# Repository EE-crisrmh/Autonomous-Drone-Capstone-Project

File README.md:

# LumaWay 🌄

> **A GPS-guided autonomous drone system that guides lost hikers back to safety.**

---

## The Problem

Every year, thousands of hikers get lost on trails across the United States. Terrain looks the same in every direction. Cell service is gone. Panic sets in. Search and rescue teams can take hours to respond — and in the mountains, hours matter.

Current solutions require hikers to stay still and wait. LumaWay flips that. Instead of waiting to be found, the hiker gets found — and then guided home.

---

## What LumaWay Does

LumaWay is an autonomous drone system built for one purpose: get a lost hiker back on the trail.

Here's how it works:

1. **Before the hike**, the hiker opens the LumaWay app and starts a session. The app passively records their GPS trail as they walk in — no interaction needed, just like a fitness tracker running in the background.

2. **If they get lost**, they hit the SOS button. The app sends their current GPS location and their recorded trail path to the LumaWay ground station.

3. **The drone launches autonomously**, navigates to the hiker's GPS coordinates, and locates them.

4. **LumaWay leads them out.** The drone flies the recorded trail path in reverse — slowly, at walking pace — using a bright LED and audio signal to guide the hiker back to the trailhead. Follow the light. That's it.

No payload to drop. No complex robotics. Just a reliable, visible guide in the sky when you need it most.

---

## Why a Drone

A drone can cover terrain a person can't. It flies over downed trees, river crossings, and steep ridgelines. It doesn't get lost. It doesn't get tired. And it can reach a hiker in minutes rather than hours.

LumaWay isn't trying to replace search and rescue — it's a first response that buys time, reduces panic, and gets people moving in the right direction before conditions get worse.

---

## The System

LumaWay is built across three integrated components:

**Custom Flight Controller (Hardware)**
A 4-layer custom PCB built around dual STM32 microcontrollers — one for navigation, one for I/O. Onboard sensors include dual IMUs (ICM-20689, ICM-20602), a barometer (MS5611), and a magnetometer (IST8310) for full attitude and altitude awareness. Designed and manufactured in-house.

**Onboard Computing (Autonomy)**
An NVIDIA Jetson Nano handles high-level autonomy — GPS waypoint navigation, computer vision for hiker confirmation, and communication with the ground station over a wireless link.

**LumaWay App (Interface)**
A mobile app for hikers. Records the trail on the way in. Sends SOS with one tap. Shows the drone's live position on a map so rescue coordinators can monitor the situation in real time.

---

## Project Goals

- Demonstrate fully autonomous GPS-guided navigation to a target location
- Achieve stable hover and guided return-path flight in outdoor conditions
- Build a functional mobile app with trail recording and SOS capability
- Integrate onboard vision for hiker detection and confirmation
- Complete a full end-to-end demo: SOS sent → drone launches → hiker guided back

---

## Status

🔧 **In development** — UW Bothell Capstone Project, 2026–2027

---

## Team

Built by a four-person Electrical Engineering capstone team at the University of Washington Bothell, supervised by Dr. Hannachi.

- Cris R. Martinez Hernandez
- Abraham Chen
- Frank Ma
- Howard Sin

---

## Built With

- STM32F405 / STM32F103 (flight controller MCUs)
- NVIDIA Jetson Nano (onboard compute)
- T-Motor MN2806 Antigravity motors
- KiCad (PCB design)
- PlatformIO (firmware)
- Python / OpenCV (computer vision)
- React Native (mobile app)

---

*LumaWay — your way home made easy*

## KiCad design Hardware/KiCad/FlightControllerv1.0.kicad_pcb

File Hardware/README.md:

Hardware files for PORT Flight Controller v1.0 + ESCs v1.0

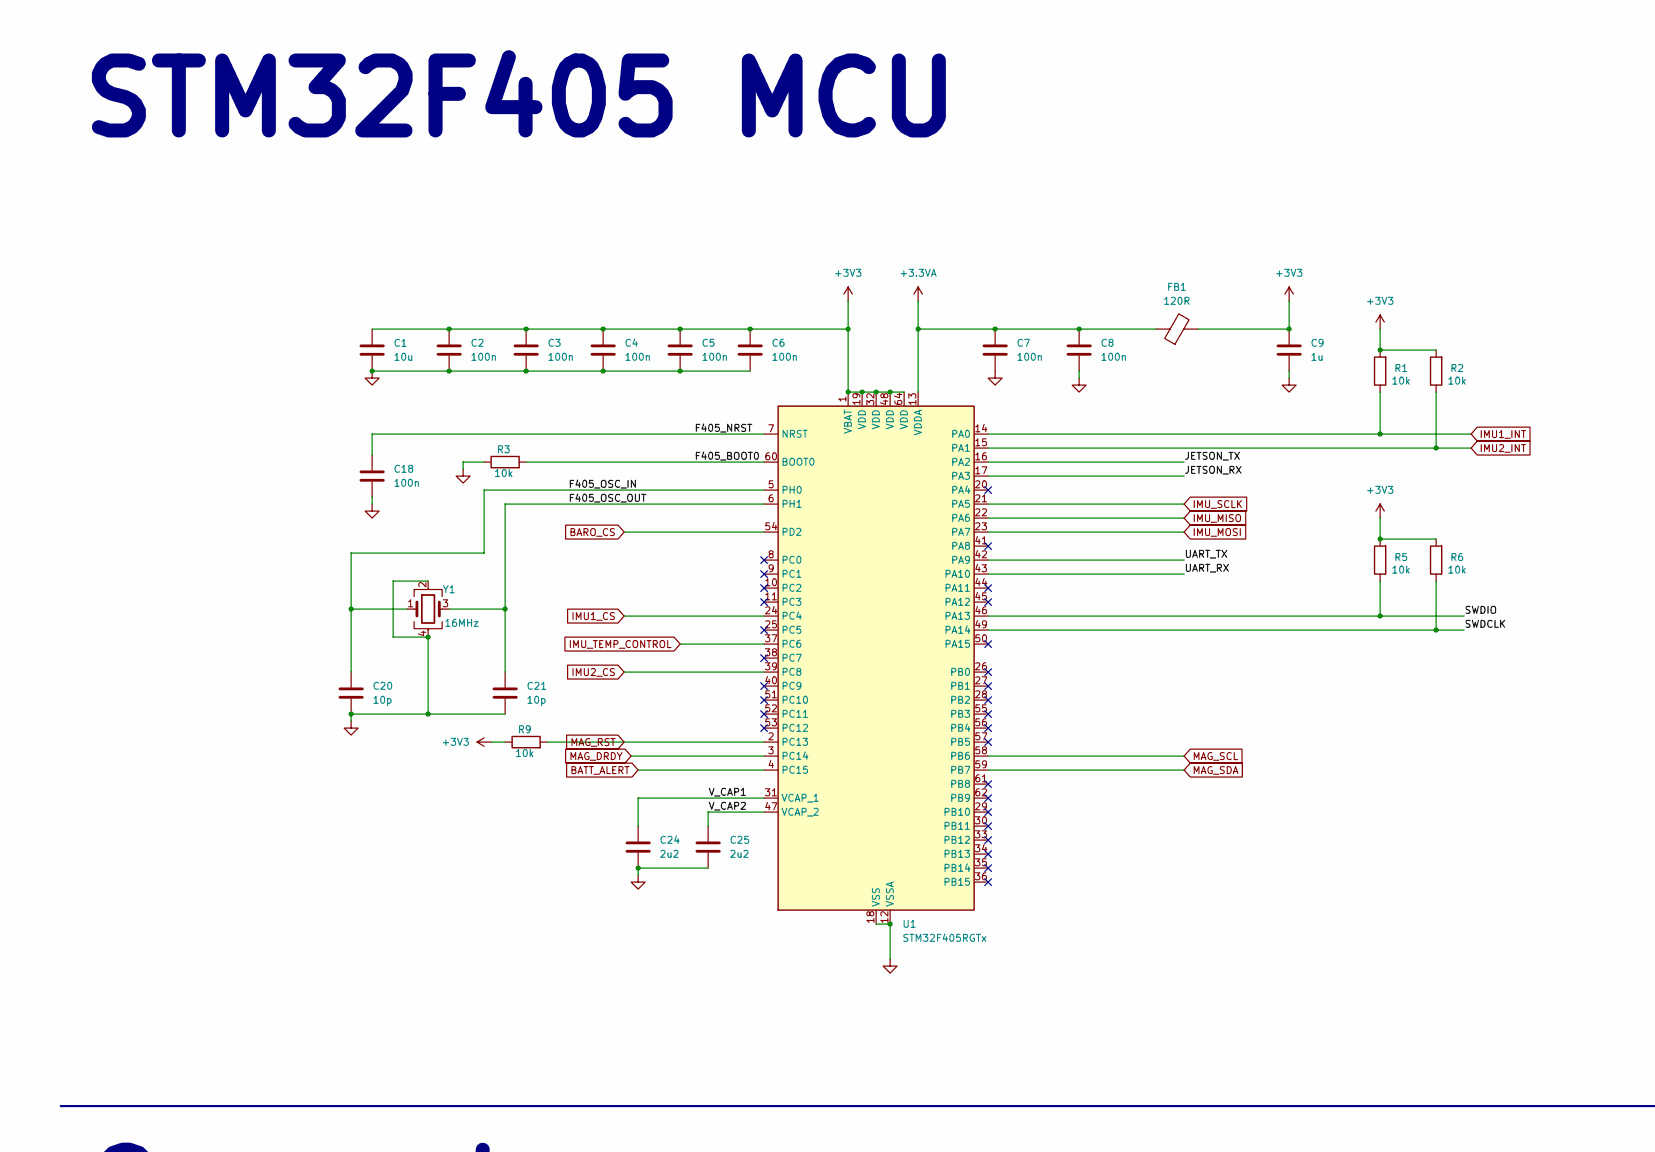
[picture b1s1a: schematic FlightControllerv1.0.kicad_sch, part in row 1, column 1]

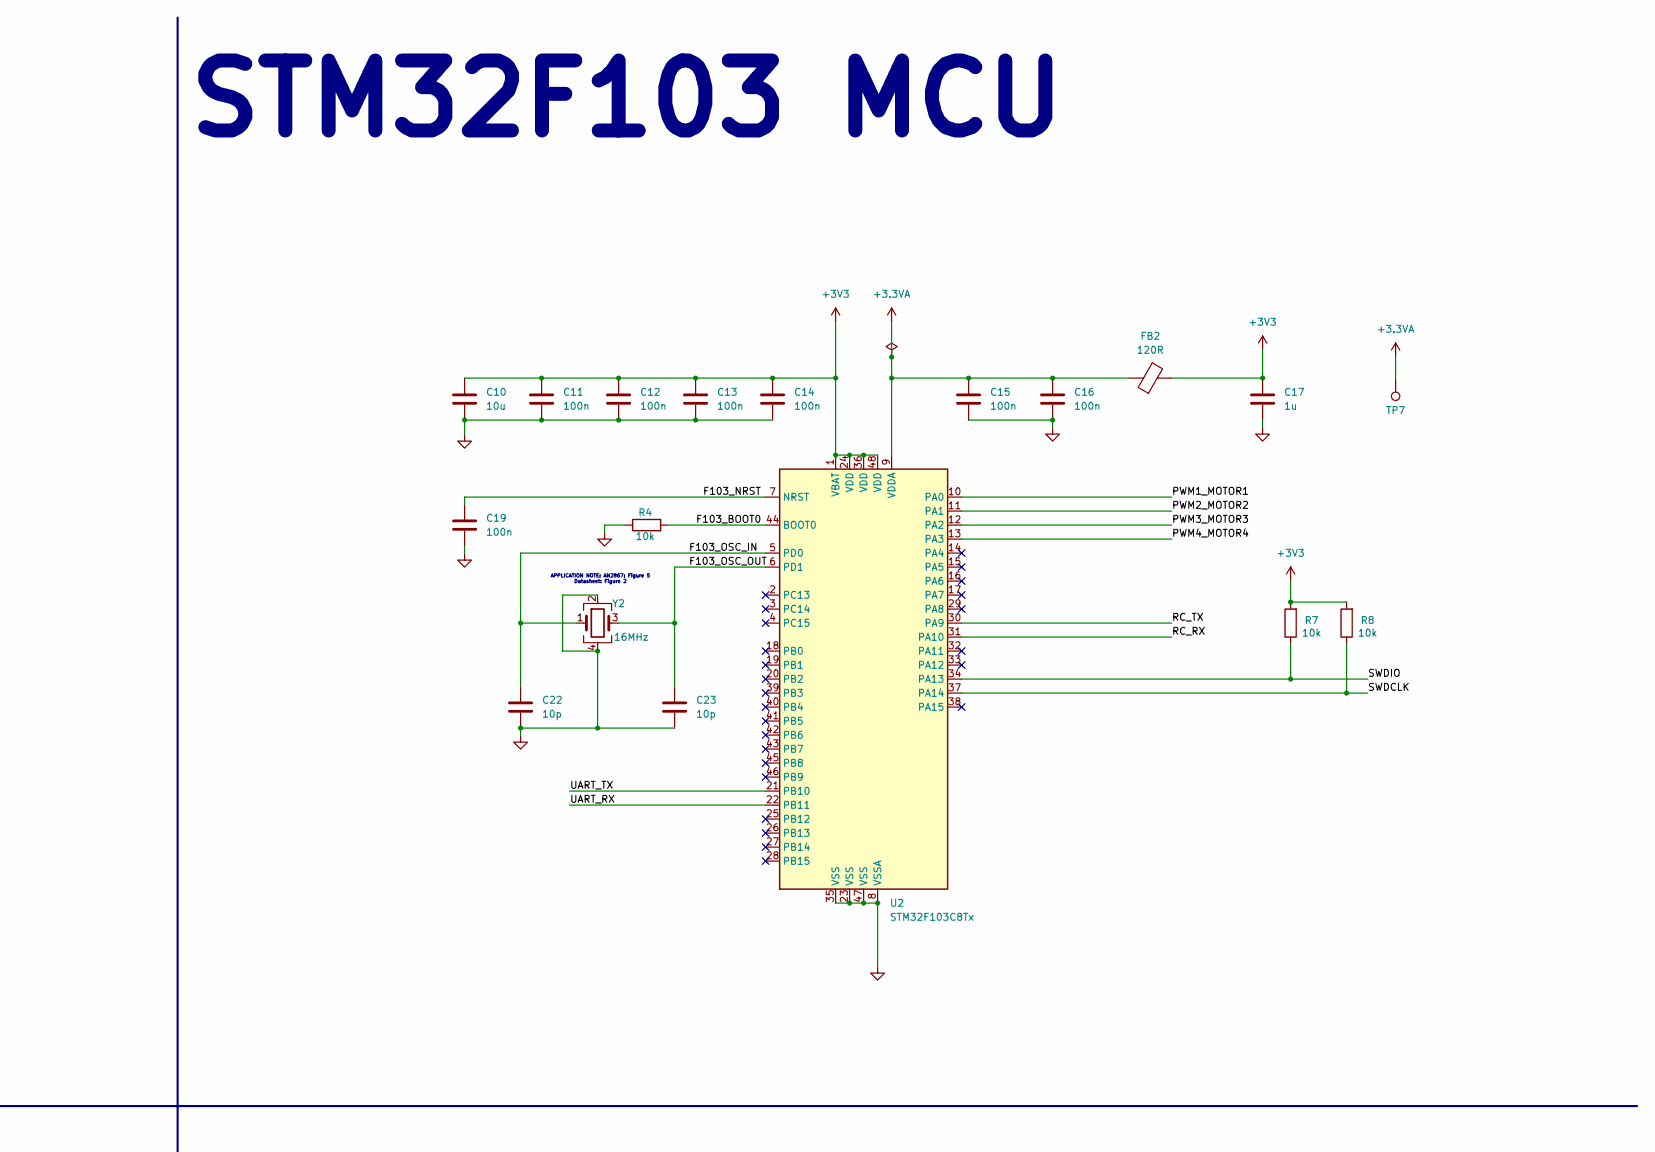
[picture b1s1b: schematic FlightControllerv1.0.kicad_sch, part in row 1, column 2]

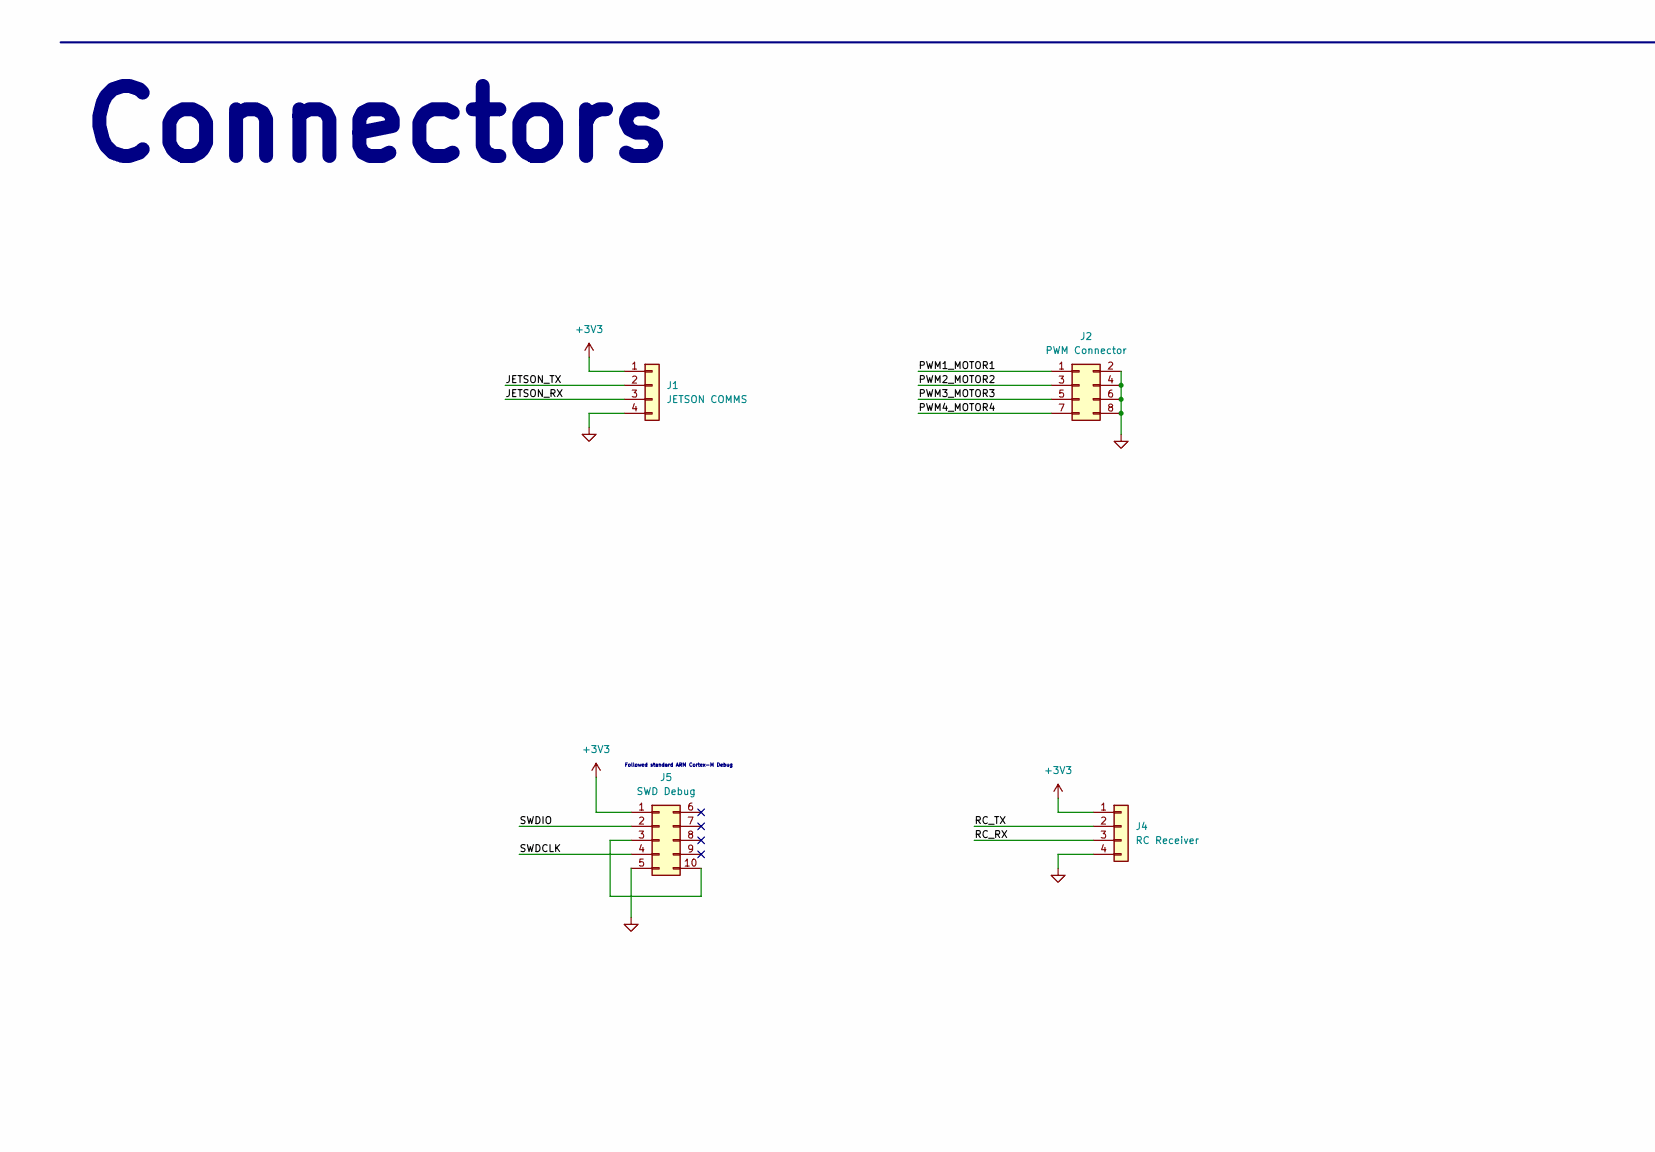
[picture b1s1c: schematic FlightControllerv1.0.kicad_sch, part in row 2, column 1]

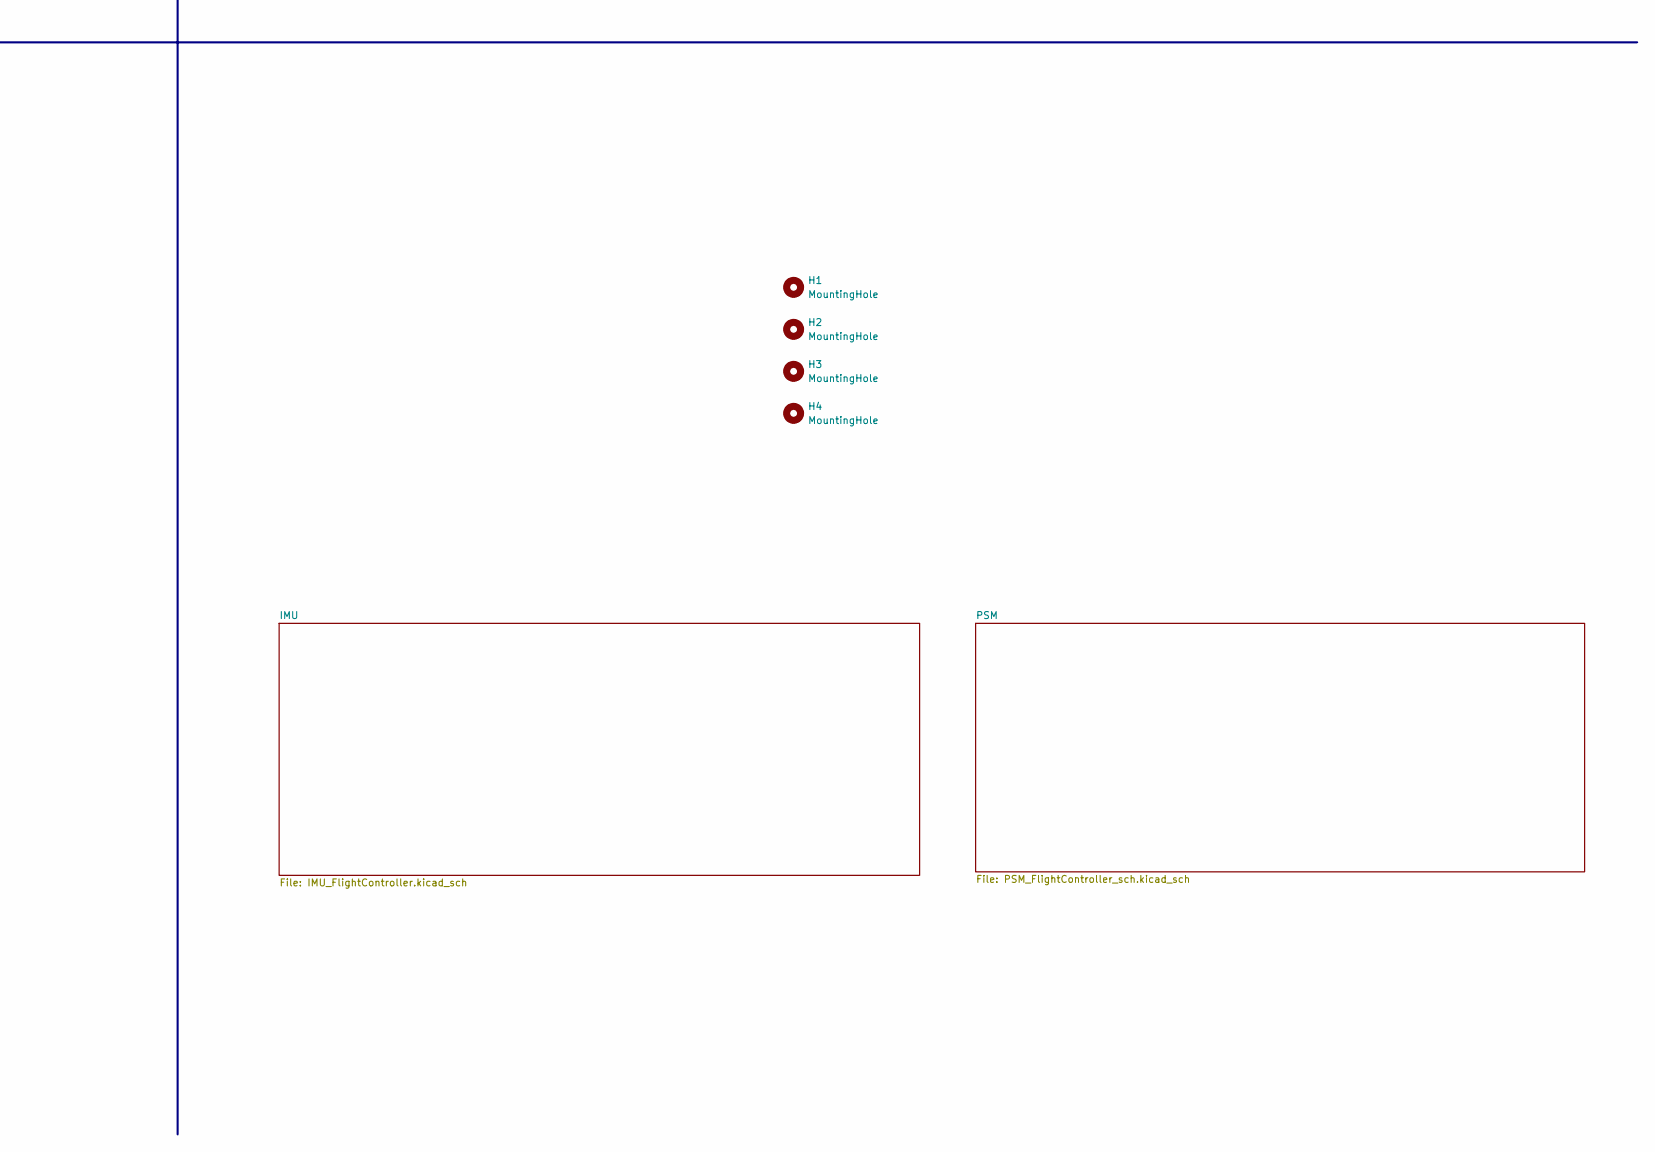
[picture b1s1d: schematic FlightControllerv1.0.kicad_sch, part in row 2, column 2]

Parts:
C1, C10: 10u; C_0603_1608Metric
C2, C3, C4, C5, C6, C7, C8, C11, C12, C13, C14, C15, C16, C18, C19: 100n; C_0402_1005Metric
C9, C17: 1u; C_0402_1005Metric
C20, C21, C22, C23: 10p; C_0402_1005Metric
C24, C25: 2u2; C_0402_1005Metric
FB1, FB2: 120R; L_0603_1608Metric
H1, H2, H3, H4: MountingHole; MountingHole_3.2mm_M3
J1: JETSON COMMS; PinHeader_1x04_P2.54mm_Vertical
J2: PWM Connector; PinHeader_2x04_P2.54mm_Vertical
J4: RC Receiver; PinHeader_1x04_P2.54mm_Vertical
J5: SWD Debug; PinHeader_2x05_P1.27mm_Vertical
R1, R2, R3, R4, R5, R6, R7, R8, R9: 10k; R_0402_1005Metric
TP7: TestPoint; TestPoint_Pad_1.0x1.0mm
U1: STM32F405RGTx; LQFP-64_10x10mm_P0.5mm
U2: STM32F103C8Tx; LQFP-48_7x7mm_P0.5mm
Y1, Y2: 16MHz; Crystal_SMD_3225-4Pin_3.2x2.5mm

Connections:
+3.3VA: C7.1, C8.1, C15.1, C16.1, FB1.1, FB2.1, TP7.1, U1.13 (VDDA), U2.9 (VDDA); also elsewhere on the board
+3V3: C1.1, C2.1, C3.1, C4.1, C5.1, C6.1, C9.1, C10.1, C11.1, C12.1, C13.1, C14.1, C17.1, FB1.2, FB2.2, J1.1, J4.1, J5.1, R1.2, R2.2, R5.2, R6.2, R7.2, R8.2, R9.1, U1.1 (VBAT), U1.19 (VDD), U1.32 (VDD), U1.48 (VDD), U1.64 (VDD), U2.1 (VBAT), U2.24 (VDD), U2.36 (VDD), U2.48 (VDD); also elsewhere on the board
/F103_BOOT0: R4.2, U2.44 (BOOT0)
/F103_NRST: C19.1, U2.7 (NRST)
/F103_OSC_IN: C22.1, U2.5 (PD0), Y2.1
/F103_OSC_OUT: C23.1, U2.6 (PD1), Y2.3
/F405_BOOT0: R3.2, U1.60 (BOOT0)
/F405_NRST: C18.1, U1.7 (NRST)
/F405_OSC_IN: C20.1, U1.5 (PH0), Y1.1
/F405_OSC_OUT: C21.1, U1.6 (PH1), Y1.3
/JETSON_RX: J1.3, U1.17 (PA3)
/JETSON_TX: J1.2, U1.16 (PA2)
/PWM1_MOTOR1: J2.1, U2.10 (PA0)
/PWM2_MOTOR2: J2.3, U2.11 (PA1)
/PWM3_MOTOR3: J2.5, U2.12 (PA2)
/PWM4_MOTOR4: J2.7, U2.13 (PA3)
/RC_RX: J4.3, U2.31 (PA10)
/RC_TX: J4.2, U2.30 (PA9)
/SWDCLK: J5.4, R6.1, R8.1, U1.49 (PA14), U2.37 (PA14)
/SWDIO: J5.2, R5.1, R7.1, U1.46 (PA13), U2.34 (PA13)
/UART_RX: U1.43 (PA10), U2.22 (PB11)
/UART_TX: U1.42 (PA9), U2.21 (PB10)
/V_CAP1: C24.1, U1.31 (VCAP_1)
/V_CAP2: C25.1, U1.47 (VCAP_2)
BARO_CS: U1.54 (PD2); also elsewhere on the board
BATT_ALERT: U1.4 (PC15); also elsewhere on the board
GND: C1.2, C2.2, C3.2, C4.2, C5.2, C6.2, C7.2, C8.2, C9.2, C10.2, C11.2, C12.2, C13.2, C14.2, C15.2, C16.2, C17.2, C18.2, C19.2, C20.2, C21.2, C22.2, C23.2, C24.2, C25.2, J1.4, J2.2, J2.4, J2.6, J2.8, J4.4, J5.5, R3.1, R4.1, U1.12 (VSSA), U1.18 (VSS), U1.63 (VSS), U2.8 (VSSA), U2.23 (VSS), U2.35 (VSS), U2.47 (VSS), Y1.2, Y1.4, Y2.2, Y2.4; also elsewhere on the board
IMU1_CS: U1.24 (PC4); also elsewhere on the board
IMU1_INT: R1.1, U1.14 (PA0); also elsewhere on the board
IMU2_CS: U1.39 (PC8); also elsewhere on the board
IMU2_INT: R2.1, U1.15 (PA1); also elsewhere on the board
IMU_MISO: U1.22 (PA6); also elsewhere on the board
IMU_MOSI: U1.23 (PA7); also elsewhere on the board
IMU_SCLK: U1.21 (PA5); also elsewhere on the board
IMU_TEMP_CONTROL: U1.37 (PC6); also elsewhere on the board
MAG_DRDY: U1.3 (PC14); also elsewhere on the board
MAG_RST: R9.2, U1.2 (PC13); also elsewhere on the board
MAG_SCL: U1.58 (PB6); also elsewhere on the board
MAG_SDA: U1.59 (PB7); also elsewhere on the board
unnamed: J5.3, J5.10

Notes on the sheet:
APPLICATION NOTE: AN2867: Figure 5 Datasheet: Figure 2
STM32F103 MCU
STM32F405 MCU
Followed standard ARM Cortex-M Debug
Connectors

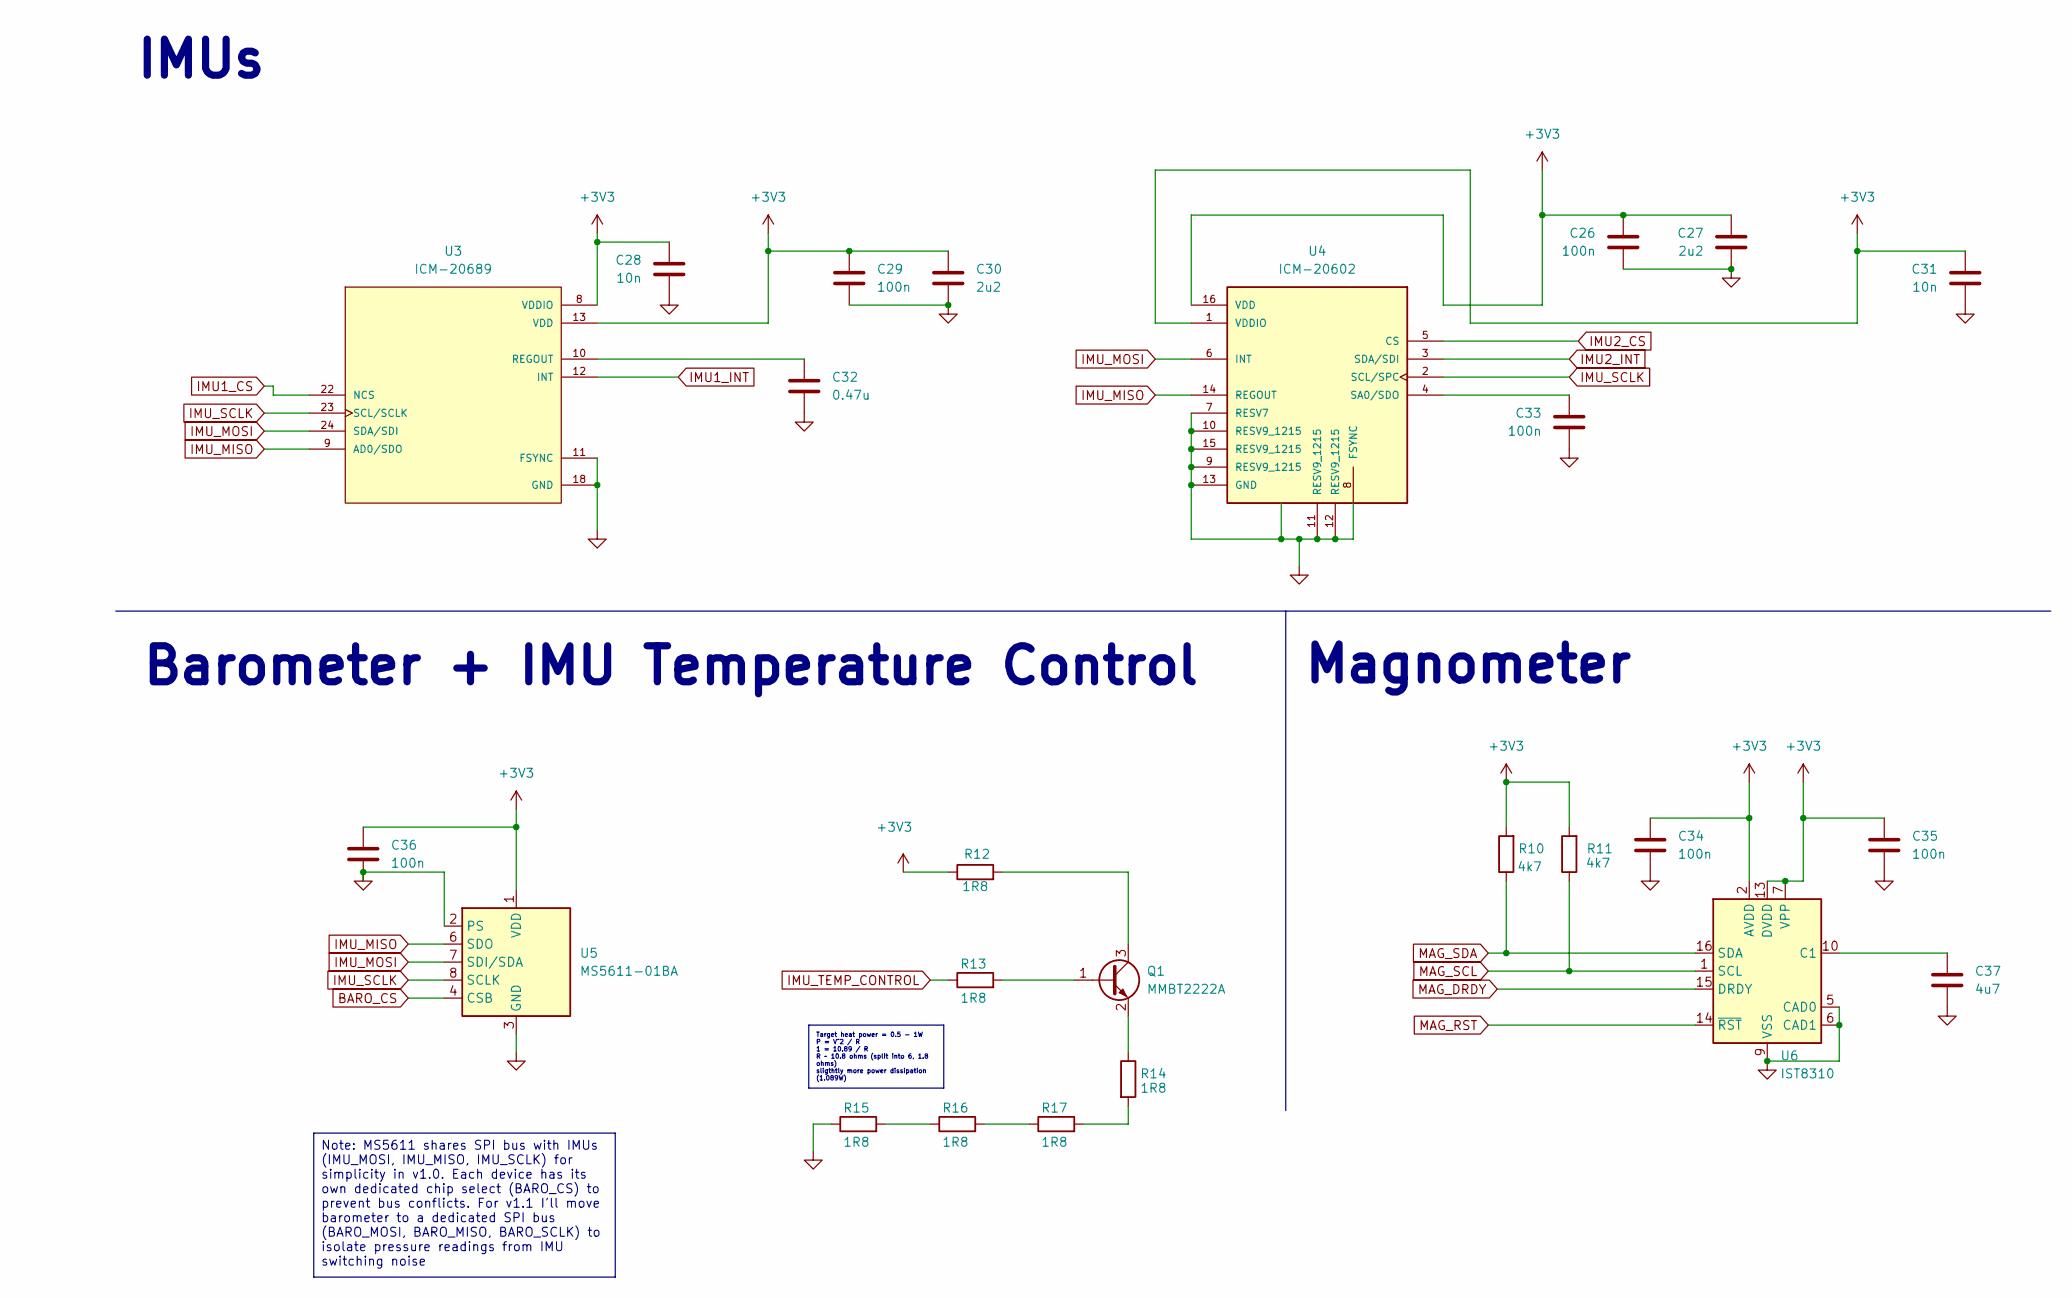
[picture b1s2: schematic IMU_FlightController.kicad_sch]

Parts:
C26, C29, C33, C34, C35, C36: 100n; C_0402_1005Metric
C27, C30: 2u2; C_0402_1005Metric
C28, C31: 10n; C_0402_1005Metric
C32: 0.47u; C_0603_1608Metric
C37: 4u7; C_0603_1608Metric
Q1: MMBT2222A; SOT-23
R10, R11: 4k7; R_0201_0603Metric
R12, R13, R14, R15, R16, R17: 1R8; R_0201_0603Metric
U3: ICM-20689; QFN-24-1EP_4x4mm_P0.5mm_EP2.65x2.65mm
U4: ICM-20602; LGA-16_3x3mm_P0.5mm
U5: MS5611-01BA; LGA-8_3x5mm_P1.25mm
U6: IST8310; LGA-16_3x3mm_P0.5mm

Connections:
+3V3: C26.1, C27.1, C28.1, C29.1, C30.1, C31.1, C34.1, C35.1, C36.1, R10.2, R11.2, R12.1, U3.8 (VDDIO), U3.13 (VDD), U4.1 (VDDIO), U4.16 (VDD), U5.1 (VDD), U6.2 (AVDD), U6.7 (VPP), U6.13 (DVDD); also elsewhere on the board
BARO_CS: U5.4 (CSB), U5.5 (CSB); also elsewhere on the board
GND: C26.2, C27.2, C28.2, C29.2, C30.2, C31.2, C32.2, C33.2, C34.2, C35.2, C36.2, C37.2, R15.1, U3.11 (FSYNC), U3.18 (GND), U4.7 (RESV7), U4.8 (FSYNC), U4.9 (RESV9_1215), U4.10 (RESV9_1215), U4.11 (RESV9_1215), U4.12 (RESV9_1215), U4.13 (GND), U4.15 (RESV9_1215), U5.2 (PS), U5.3 (GND), U6.5 (CAD0), U6.6 (CAD1), U6.9 (VSS), U6.11 (VSS); also elsewhere on the board
IMU1_CS: U3.22 (NCS); also elsewhere on the board
IMU1_INT: U3.12 (INT); also elsewhere on the board
IMU2_CS: U4.5 (CS); also elsewhere on the board
IMU2_INT: U4.3 (SDA/SDI); also elsewhere on the board
IMU_MISO: U3.9 (AD0/SDO), U4.14 (REGOUT), U5.6 (SDO); also elsewhere on the board
IMU_MOSI: U3.24 (SDA/SDI), U4.6 (INT), U5.7 (SDI/SDA); also elsewhere on the board
IMU_SCLK: U3.23 (SCL/SCLK), U4.2 (SCL/SPC), U5.8 (SCLK); also elsewhere on the board
IMU_TEMP_CONTROL: R13.1; also elsewhere on the board
MAG_DRDY: U6.15 (DRDY); also elsewhere on the board
MAG_RST: U6.14 (~RST); also elsewhere on the board
MAG_SCL: R11.1, U6.1 (SCL); also elsewhere on the board
MAG_SDA: R10.1, U6.16 (SDA); also elsewhere on the board
unnamed: Q1.1 (B), R13.2
unnamed: Q1.3 (C), R12.2
unnamed: Q1.2 (E), R14.1
unnamed: R14.2, R17.2
unnamed: R15.2, R16.1
unnamed: R16.2, R17.1
unnamed: C32.1, U3.10 (REGOUT)
unnamed: C33.1, U4.4 (SA0/SDO)
unnamed: C37.1, U6.10 (C1)

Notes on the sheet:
Barometer + IMU Temperature Control
Magnometer
IMUs
Note: MS5611 shares SPI bus with IMUs (IMU_MOSI, IMU_MISO, IMU_SCLK) for simplicity in v1.0. Each device has its own dedicated chip select (BARO_CS) to prevent bus conflicts. For v1.1 I'll move barometer to a dedicated SPI bus (BARO_MOSI, BARO_MISO, BARO_SCLK) to isolate pressure readings from IMU 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
Target heat power = 0.5 - 1W P = V^2 / R 1 = 10.89 / R R ~ 10.8 ohms (split into 6, 1.8 ohms) sligthtly more power dissipation (1.089W)

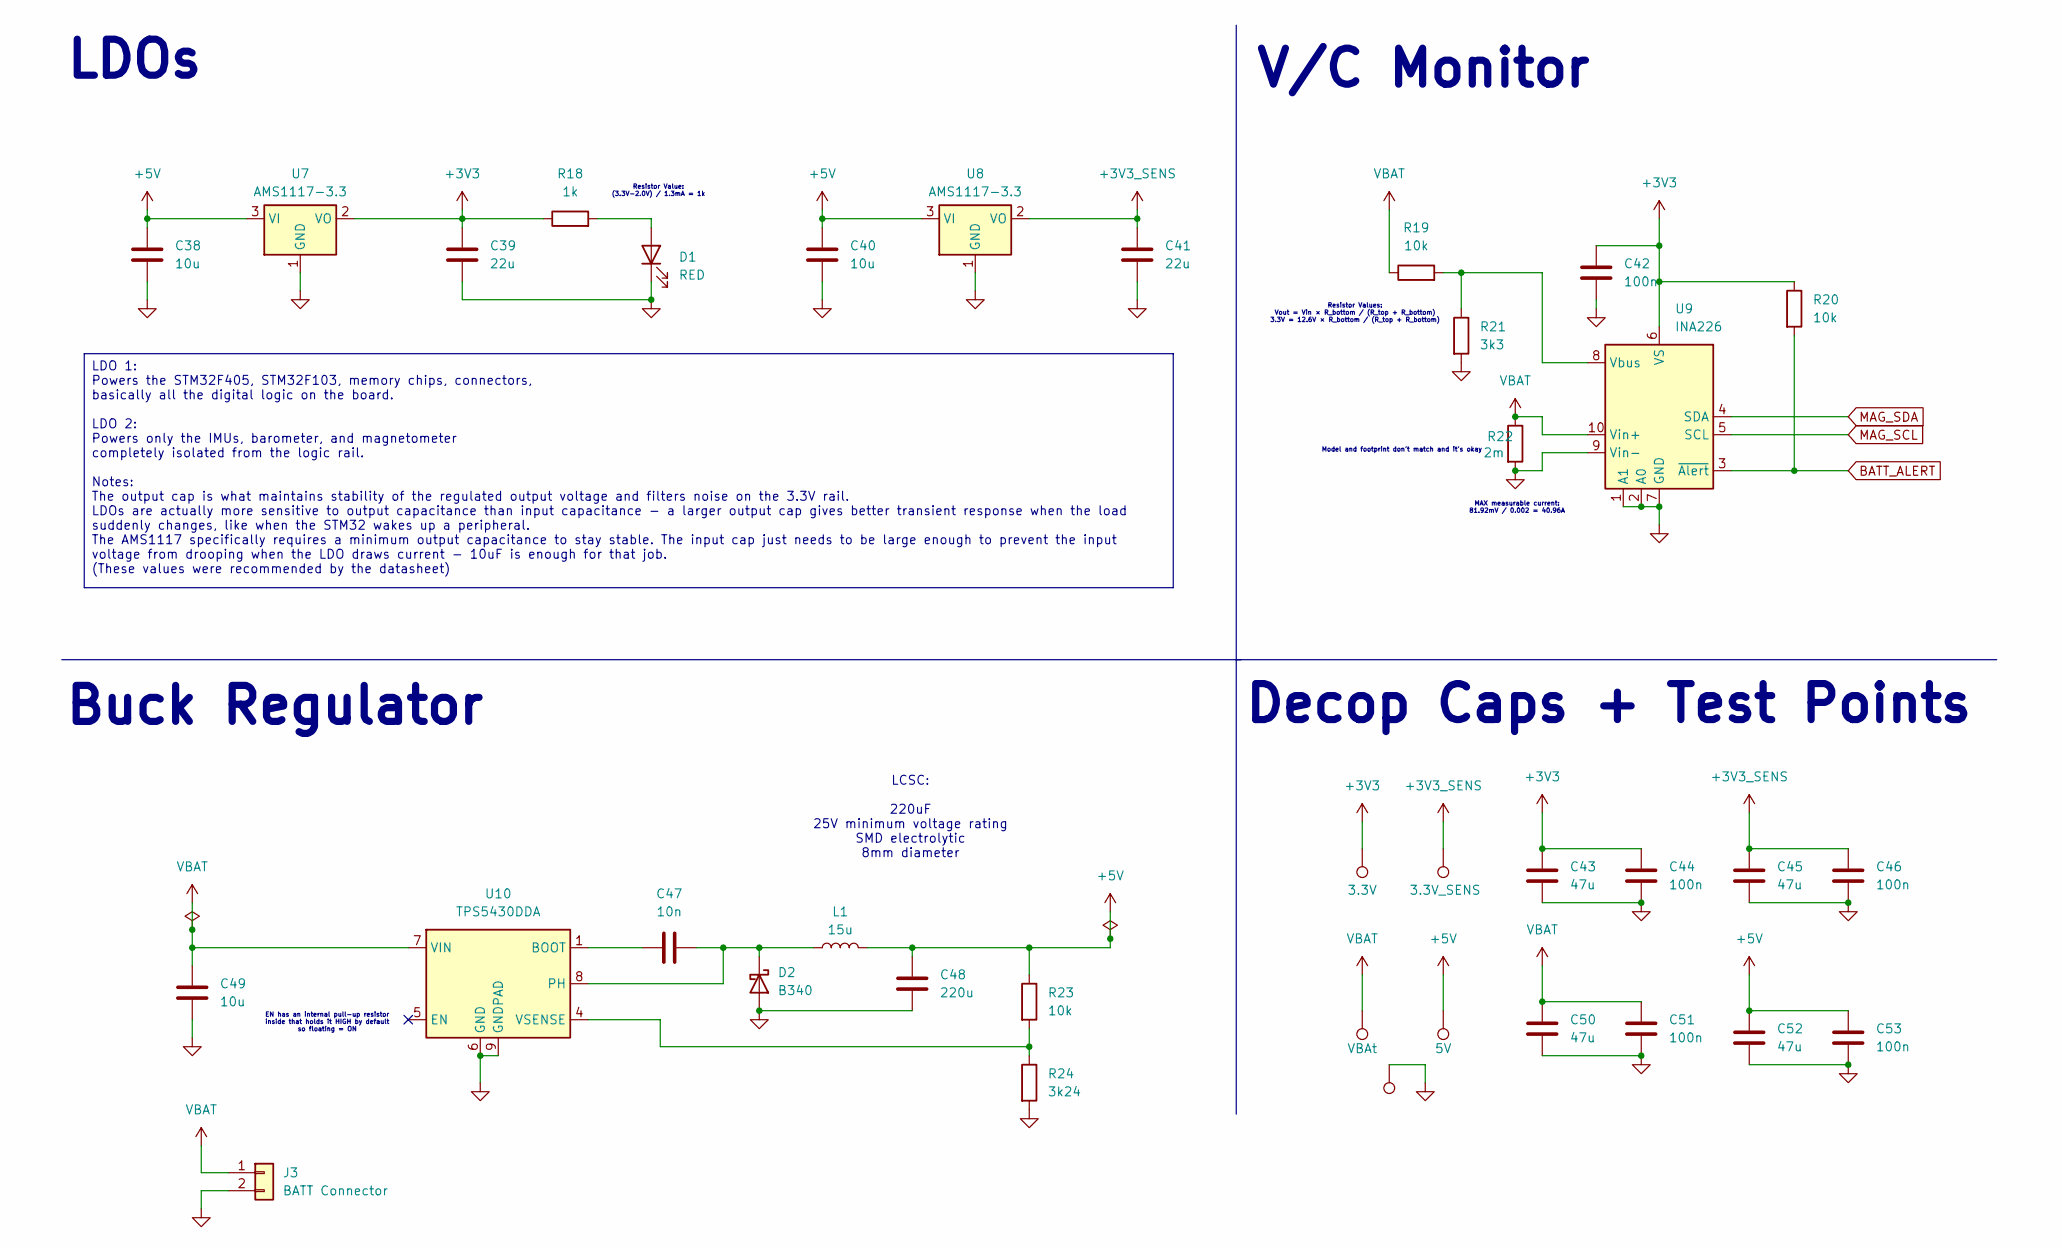
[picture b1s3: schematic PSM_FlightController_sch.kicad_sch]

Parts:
3.3V, 3.3V_SENS, 5V: TestPoint; TestPoint_Pad_1.0x1.0mm
C38, C40, C49: 10u; C_0603_1608Metric
C39, C41: 22u; C_0805_2012Metric
C42, C44, C46, C51, C53: 100n; C_0402_1005Metric
C43, C45, C50, C52: 47u; C_0805_2012Metric
C47: 10n; C_0402_1005Metric
C48: 220u; CP_Elec_8x10.5
D1: RED; LED_0805_2012Metric
D2: B340; D_SMA
J3: BATT Connector; AMASS_XT60PW-F_1x02_P7.20mm_Horizontal
L1: 15u; L_2512_6332Metric
R18: 1k; R_0402_1005Metric
R19, R20, R23: 10k; R_0402_1005Metric
R21: 3k3; R_0402_1005Metric
R22: 2m; R_Shunt_Vishay_WSK2512_6332Metric_T1.19mm
R24: 3k24; R_0402_1005Metric
TP5: TestPoint; TestPoint_Pad_1.0x1.0mm
U7, U8: AMS1117-3.3; SOT-223-3_TabPin2
U9: INA226; VSSOP-10_3x3mm_P0.5mm
U10: TPS5430DDA; TI_SO-PowerPAD-8_ThermalVias
VBAt: TestPoint; TestPoint_Pad_1.0x1.0mm

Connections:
+3V3: 3.3V.1, C39.1, C42.2, C43.2, C44.2, R18.1, R20.1, U7.2 (VO), U9.6 (VS); also elsewhere on the board
+3V3_SENS: 3.3V_SENS.1, C41.1, C45.2, C46.2, U8.2 (VO)
+5V: 5V.1, C38.1, C40.1, C48.2, C52.2, C53.2, L1.2, R23.1, U7.3 (VI), U8.3 (VI)
BATT_ALERT: R20.2, U9.3 (~Alert); also elsewhere on the board
GND: C38.2, C39.2, C40.2, C41.2, C42.1, C43.1, C44.1, C45.1, C46.1, C48.1, C49.2, C50.1, C51.1, C52.1, C53.1, D1.1 (K), D2.2 (A), J3.2, R21.2, R22.2, R24.2, TP5.1, U7.1 (GND), U8.1 (GND), U9.1 (A1), U9.2 (A0), U9.7 (GND), U9.9 (Vin-), U10.6 (GND), U10.9 (GNDPAD); also elsewhere on the board
MAG_SCL: U9.5 (SCL); also elsewhere on the board
MAG_SDA: U9.4 (SDA); also elsewhere on the board
unnamed: D1.2 (A), R18.2
unnamed: C47.2, D2.1 (K), L1.1, U10.8 (PH)
unnamed: R19.2, R21.1, U9.8 (Vbus)
unnamed: C47.1, U10.1 (BOOT)
unnamed: R23.2, R24.1, U10.4 (VSENSE)
VBAT: C49.1, C50.2, C51.2, J3.1, R19.1, R22.1, U9.10 (Vin+), U10.7 (VIN), VBAt.1; also elsewhere on the board

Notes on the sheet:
LCSC: 220uF 25V minimum voltage rating SMD electrolytic 8mm diameter
Buck Regulator
Resistor Values: Vout = Vin × R_bottom / (R_top + R_bottom) 3.3V = 12.6V × R_bottom / (R_top + R_bottom)
Model and footprint don't match and it's okay
Resistor Value: (3.3V-2.0V) / 1.3mA = 1k
V/C Monitor
EN has an internal pull-up resistor inside that holds it HIGH by default so floating = ON
MAX measurable current: 81.92mV / 0.002 = 40.96A
Decop Caps + Test Points
LDOs
LDO 1: Powers the STM32F405, STM32F103, memory chips, connectors, basically all the digital logic on the board. LDO 2: Powers only the IMUs, barometer, and magnetometer completely isolated from the logic rail. Notes: The output cap is what maintains stability of the regulated output voltage and fil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
